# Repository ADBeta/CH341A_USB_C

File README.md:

# CH341a USB-C Breakout Board with UART and Programmer Pinouts

## Description
A Breakout Board for the CH341a USB UART, I2C and SPI Device, used for
programming SPI Flash Storage or I2C EEPROM, but with USB-C Connector
rather than the USB-A Male of the generic `Black Edition` Board.

<div style="display: flex; align-items: center; gap: 10px;">
  <br>

</div>  

## Parts List
```
D1      0603 Red LED
D2      0603 Red LED

R1      0603 2K2
R2      0603 2K2
R3      0603 2K2
R4      0603 2K2

C1      0603 20pF
C2      0603 20pF
C3      0603 100nF

U1      CH341a
U2      AMS1117-3.3

Y1      HC49S 12MHz XTAL
```

----
Copyright (c) ADBeta 2025

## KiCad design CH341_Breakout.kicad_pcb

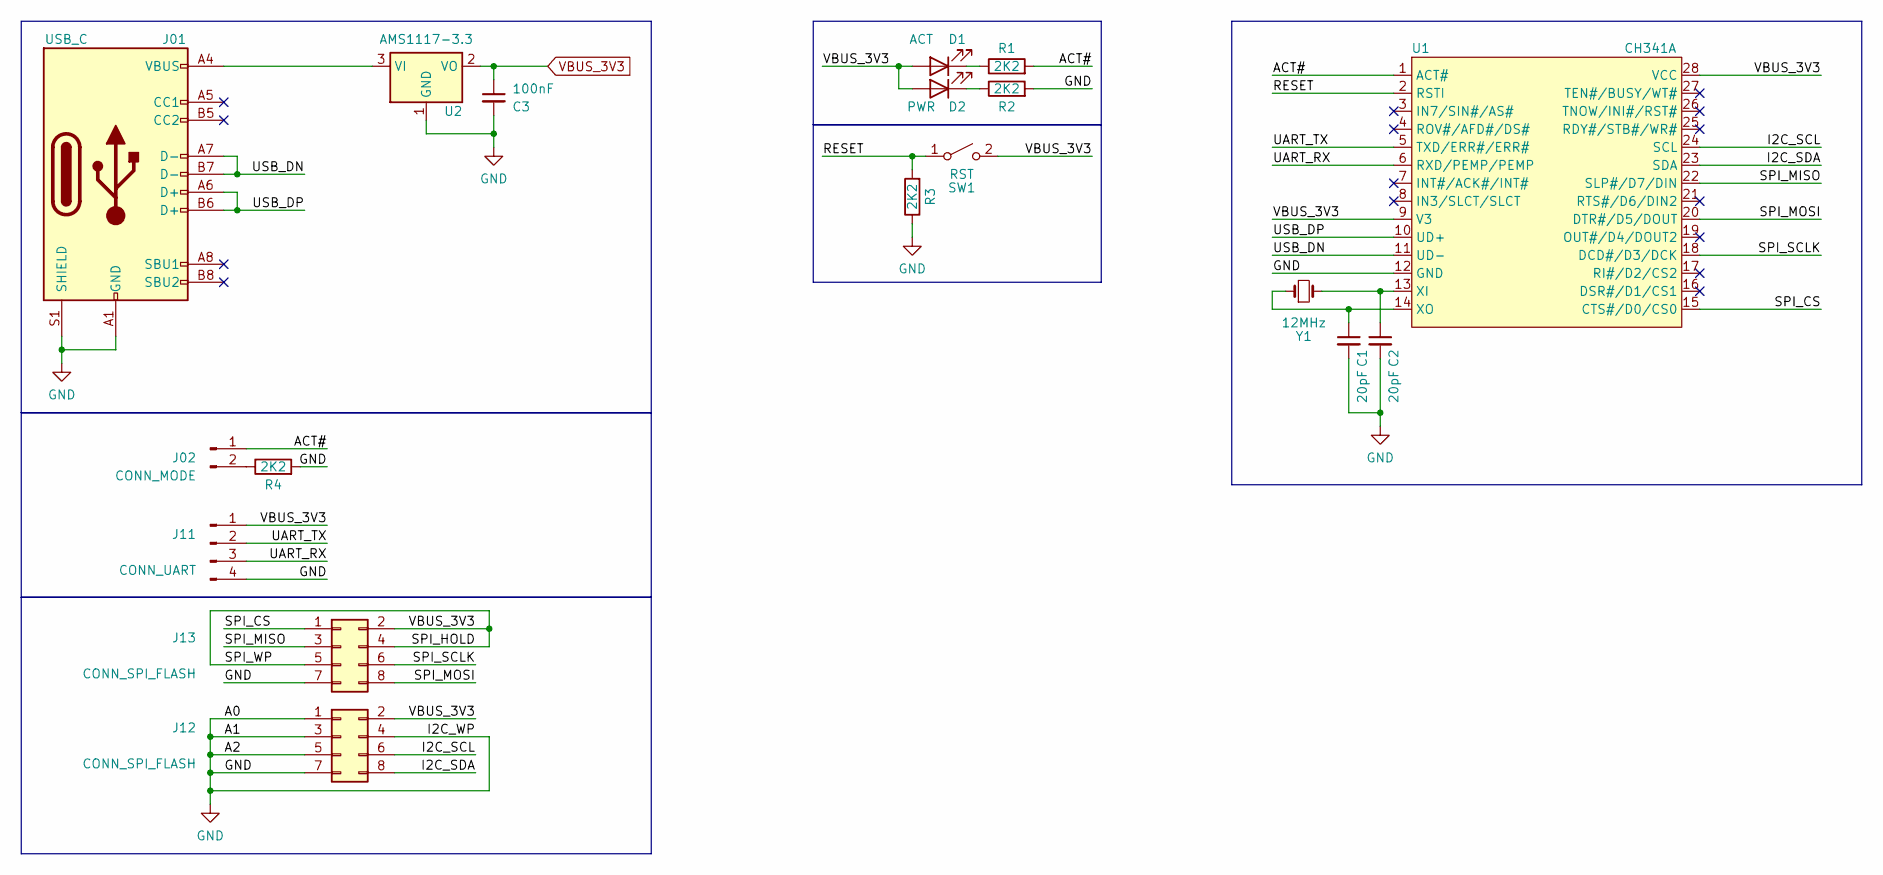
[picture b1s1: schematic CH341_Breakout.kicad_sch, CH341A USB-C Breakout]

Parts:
C1, C2: 20pF; C_0603_1608Metric
C3: 100nF; C_0603_1608Metric
D1: ACT; LED_0603_1608Metric
D2: PWR; LED_0603_1608Metric
J01: USB_C; USB_C_Receptacle_G-Switch_GT-USB-7010ASV
J02: CONN_MODE; PinHeader_1x02_P2.54mm_Vertical
J11: CONN_UART; PinHeader_1x04_P2.54mm_Vertical
J12, J13: CONN_SPI_FLASH
R1, R2, R3, R4: 2K2; R_0603_1608Metric
SW1: RST; SW_SPST_SKQG_WithoutStem
U1: CH341A; SOIC-28W_7.5x17.9mm_P1.27mm
U2: AMS1117-3.3; SOT-223-3_TabPin2
Y1: 12MHz; Crystal_HC49-U_Vertical

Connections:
/ACT#: J02.1, R1.2, U1.1 (ACT#)
/I2C_SCL: J12.6, U1.24 (SCL)
/I2C_SDA: J12.8, U1.23 (SDA)
/RESET: R3.2, SW1.1 (A), U1.2 (RSTI)
/SPI_CS: J13.1, U1.15 (CTS#/D0/CS0)
/SPI_MISO: J13.3, U1.22 (SLP#/D7/DIN)
/SPI_MOSI: J13.8, U1.20 (DTR#/D5/DOUT)
/SPI_SCLK: J13.6, U1.18 (DCD#/D3/DCK)
/UART_RX: J11.3, U1.6 (RXD/PEMP/PEMP)
/UART_TX: J11.2, U1.5 (TXD/ERR#/ERR#)
/USB_DN: J01.A7 (D-), J01.B7 (D-), U1.11 (UD-)
/USB_DP: J01.A6 (D+), J01.B6 (D+), U1.10 (UD+)
GND: C1.2, C2.2, C3.2, J01.A1 (GND), J01.A12 (GND), J01.B1 (GND), J01.B12 (GND), J01.S1 (SHIELD), J11.4, J12.1, J12.3, J12.4, J12.5, J12.7, J13.7, R2.2, R3.1, R4.2, U1.12 (GND), U2.1 (GND)
unnamed: D1.1 (K), R1.1
unnamed: D2.1 (K), R2.1
unnamed: J02.2, R4.1
unnamed: C2.1, U1.13 (XI), Y1.2
unnamed: C1.1, U1.14 (XO), Y1.1
unnamed: J01.A4 (VBUS), J01.A9 (VBUS), J01.B4 (VBUS), J01.B9 (VBUS), U2.3 (VI)
VBUS_3V3: C3.1, D1.2 (A), D2.2 (A), J11.1, J12.2, J13.2, J13.4, J13.5, SW1.2 (B), U1.9 (V3), U1.28 (VCC), U2.2 (VO)

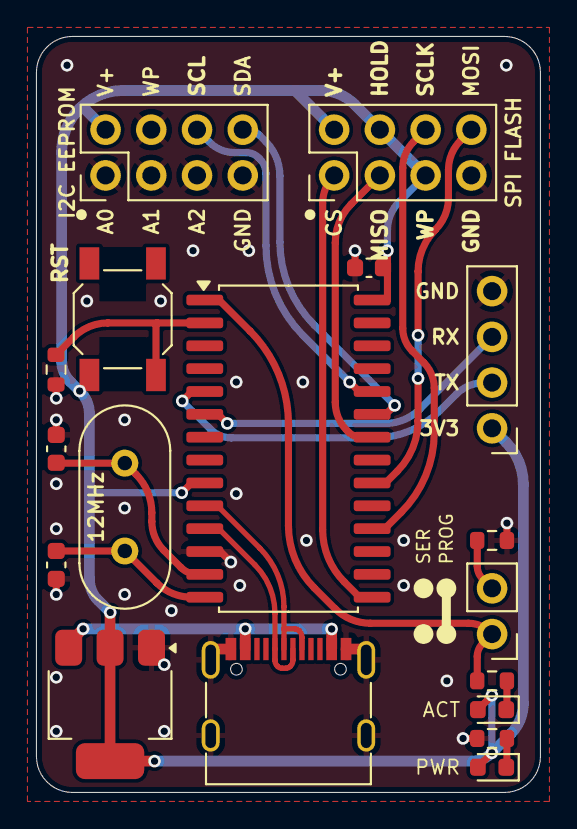
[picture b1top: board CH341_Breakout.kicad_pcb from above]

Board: 2 copper layers, 28.0 x 42.0 mm, 18 parts (0 on the bottom side), 20 nets.

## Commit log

2025-04-24 Added USB C and other bits
2025-04-26 Started MkI PCB Design
2025-04-28 Finished MkI Board
2025-04-28 Added README
2025-04-28 Fixed README
2025-05-09 Finalised, built and tested
